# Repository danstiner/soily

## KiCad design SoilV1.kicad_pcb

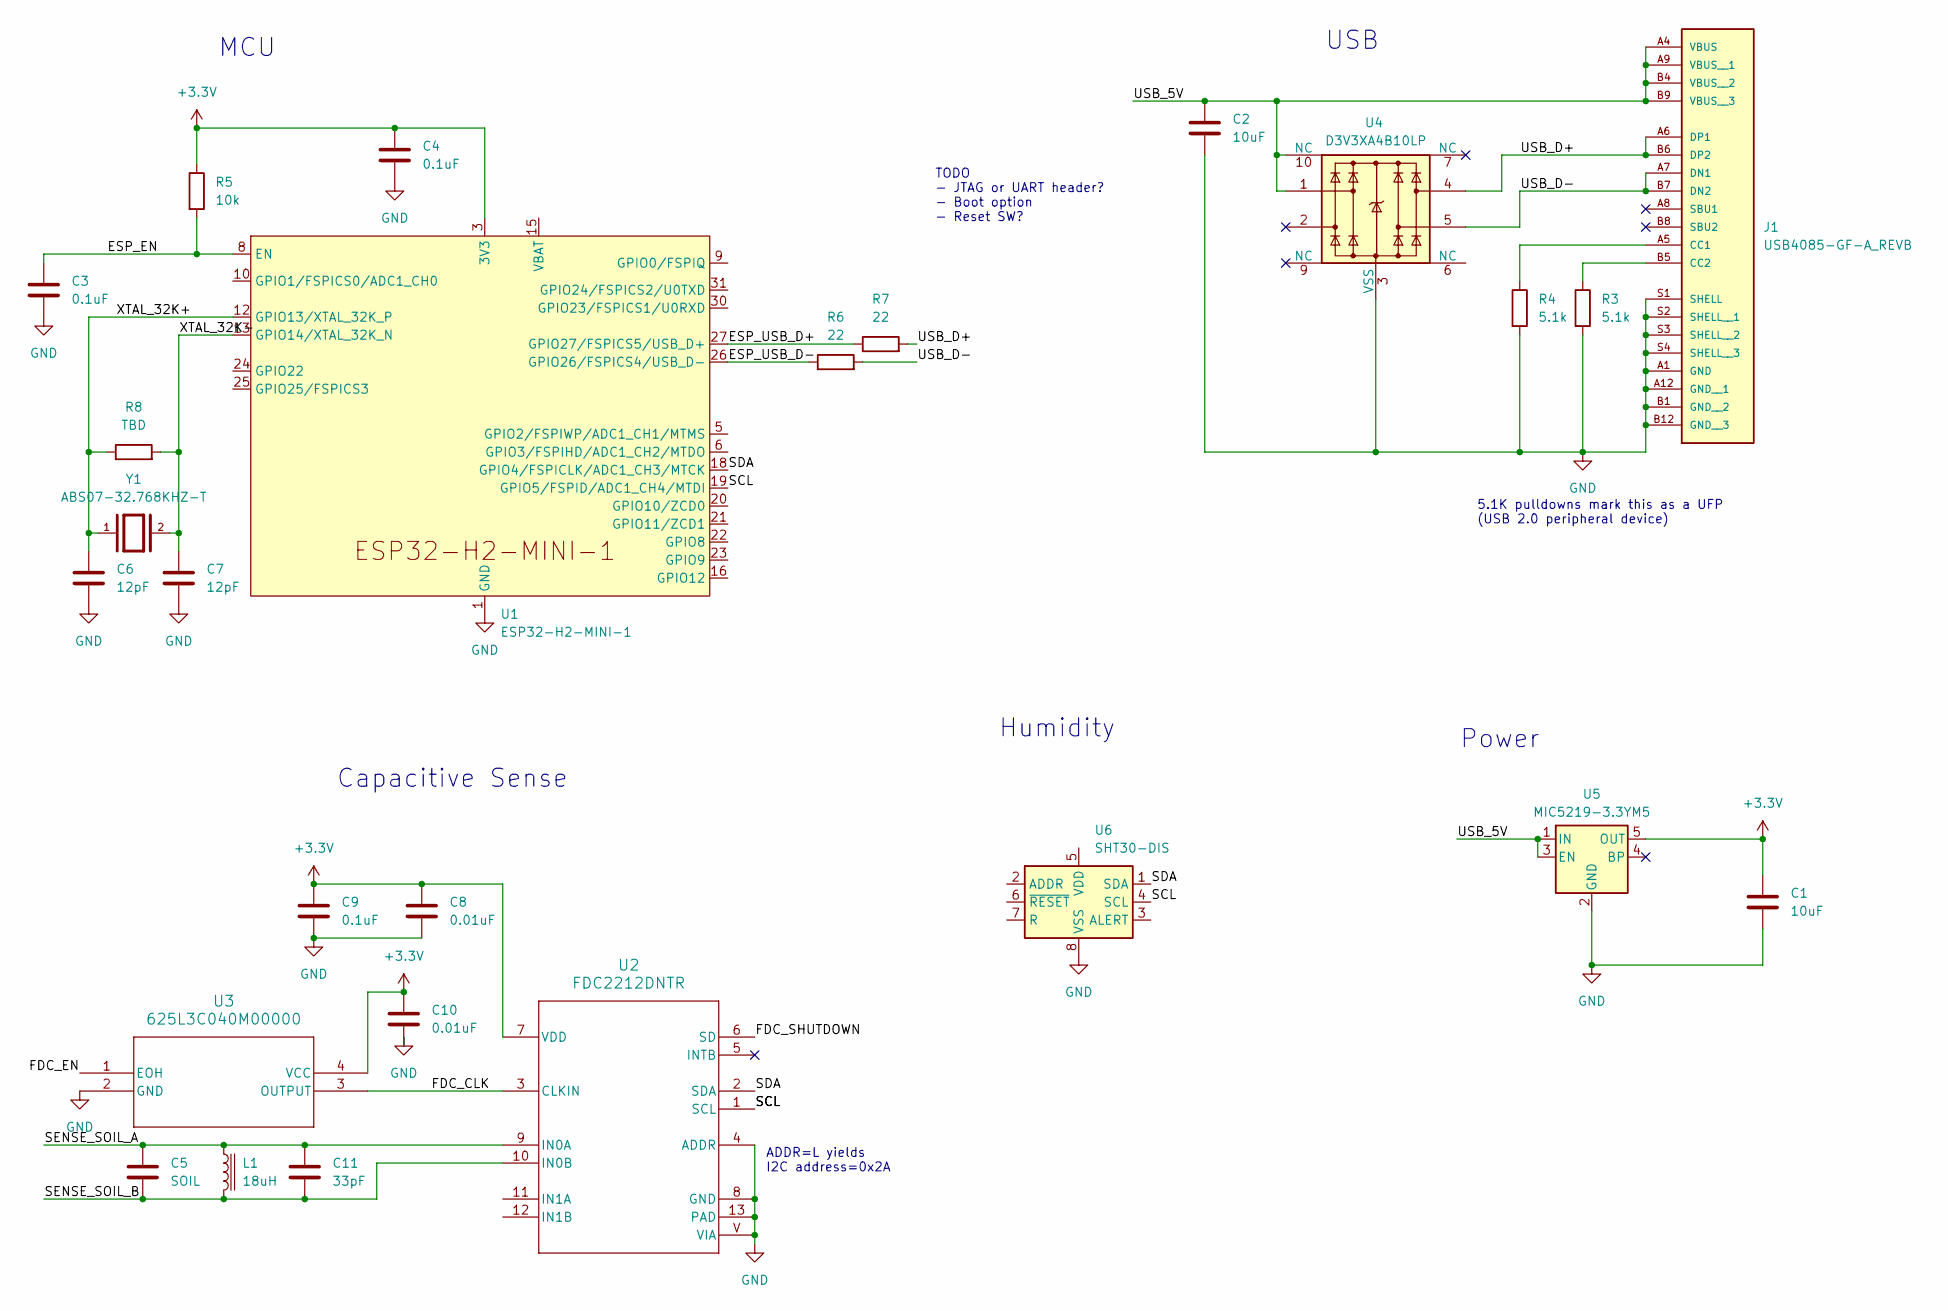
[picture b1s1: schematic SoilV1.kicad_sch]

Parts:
C1, C2: 10uF; C_0805_2012Metric
C3, C4, C9: 0.1uF; C_0402_1005Metric
C5: SOIL; C_Rectangle
C6, C7: 12pF; C_0402_1005Metric
C8, C10: 0.01uF; C_0402_1005Metric
C11: 33pF; C_0603_1608Metric
J1: USB4085-GF-A_REVB; GCT_USB4085-GF-A_REVB; PARTREV B
L1: 18uH; L_0603_1608Metric
R3, R4: 5.1k; R_0402_1005Metric
R5: 10k; R_0402_1005Metric
R6, R7: 22; R_0402_1005Metric
R8: TBD; R_0402_1005Metric
U1: ESP32-H2-MINI-1
U2: FDC2212DNTR; DNT0012B
U3: 625L3C040M00000; IC_625L3C040M00000_CTS
U4: D3V3XA4B10LP; Diodes_UDFN-10_1.0x2.5mm_P0.5mm
U5: MIC5219-3.3YM5; SOT-23-5
U6: SHT30-DIS; Sensirion_DFN-8-1EP_2.5x2.5mm_P0.5mm_EP1.1x1.7mm
Y1: ABS07-32.768KHZ-T; XTAL_ABS07-32.768KHZ-T; PARTREV 08.19.15

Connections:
+3.3V: C1.1, C4.1, C8.1, C9.1, C10.1, R5.1, U1.3 (3V3), U2.7 (VDD), U3.4 (VCC), U5.5 (OUT)
/ESP_EN: C3.1, R5.2, U1.8 (EN)
/ESP_USB_D+: R7.1, U1.27 (GPIO27/FSPICS5/USB_D+)
/ESP_USB_D-: R6.1, U1.26 (GPIO26/FSPICS4/USB_D-)
/FDC_CLK: U2.3 (CLKIN), U3.3 (OUTPUT)
/FDC_EN: U3.1 (EOH)
/FDC_SHUTDOWN: U2.6 (SD)
/SCL: U1.19 (GPIO5/FSPID/ADC1_CH4/MTDI), U2.1 (SCL), U6.4 (SCL)
/SDA: U1.18 (GPIO4/FSPICLK/ADC1_CH3/MTCK), U2.2 (SDA), U6.1 (SDA)
/SENSE_SOIL_A: C5.1, C11.1, L1.1, U2.9 (IN0A)
/SENSE_SOIL_B: C5.2, C11.2, L1.2, U2.10 (IN0B)
/USB_5V: C2.1, J1.A4 (VBUS), J1.A9 (VBUS__1), J1.B4 (VBUS__2), J1.B9 (VBUS__3), U4.1, U4.10 (NC), U5.1 (IN), U5.3 (EN)
/USB_D+: J1.A6 (DP1), J1.B6 (DP2), R7.2, U4.4
/USB_D-: J1.A7 (DN1), J1.B7 (DN2), R6.2, U4.5
/XTAL_32K+: C6.1, R8.1, U1.12 (GPIO13/XTAL_32K_P), Y1.1
/XTAL_32K-: C7.1, R8.2, U1.13 (GPIO14/XTAL_32K_N), Y1.2
GND: C1.2, C2.2, C3.2, C4.2, C6.2, C7.2, C8.2, C9.2, C10.2, J1.A1 (GND), J1.A12 (GND__1), J1.B1 (GND__2), J1.B12 (GND__3), J1.S1 (SHELL), J1.S2 (SHELL__1), J1.S3 (SHELL__2), J1.S4 (SHELL__3), R3.2, R4.2, U1.1 (GND), U1.2 (GND), U1.11 (GND), U1.14 (GND), U1.36 (GND), U1.37 (GND), U1.38 (GND), U1.39 (GND), U1.40 (GND), U1.41 (GND), U1.42 (GND), U1.43 (GND), U1.44 (GND), U1.45 (GND), U1.46 (GND), U1.47 (GND), U1.48 (GND), U1.49 (GND), U1.50 (GND), U1.51 (GND), U1.52 (GND), U1.53 (GND), U2.4 (ADDR), U2.8 (GND), U2.13 (PAD), U2.V (VIA), U3.2 (GND), U4.3 (VSS), U4.8 (VSS), U5.2 (GND), U6.8 (VSS), U6.9 (VSS)
unnamed: J1.A5 (CC1), R4.1
unnamed: J1.B5 (CC2), R3.1

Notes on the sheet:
Capacitive Sense
Power
Humidity
USB
5.1K pulldowns mark this as a UFP (USB 2.0 peripheral device)
MCU
ADDR=L yields I2C address=0x2A
TODO - JTAG or UART header? - Boot option - Reset SW?

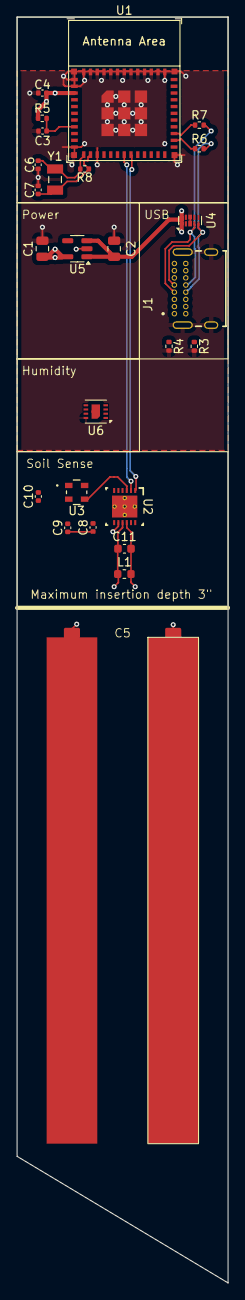
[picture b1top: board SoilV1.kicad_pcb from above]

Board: 4 copper layers, 25.0 x 150.0 mm, 26 parts (0 on the bottom side), 17 nets.
